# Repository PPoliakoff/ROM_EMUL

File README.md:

# ROM_EMUL
An emulator for the 27256 EPROM

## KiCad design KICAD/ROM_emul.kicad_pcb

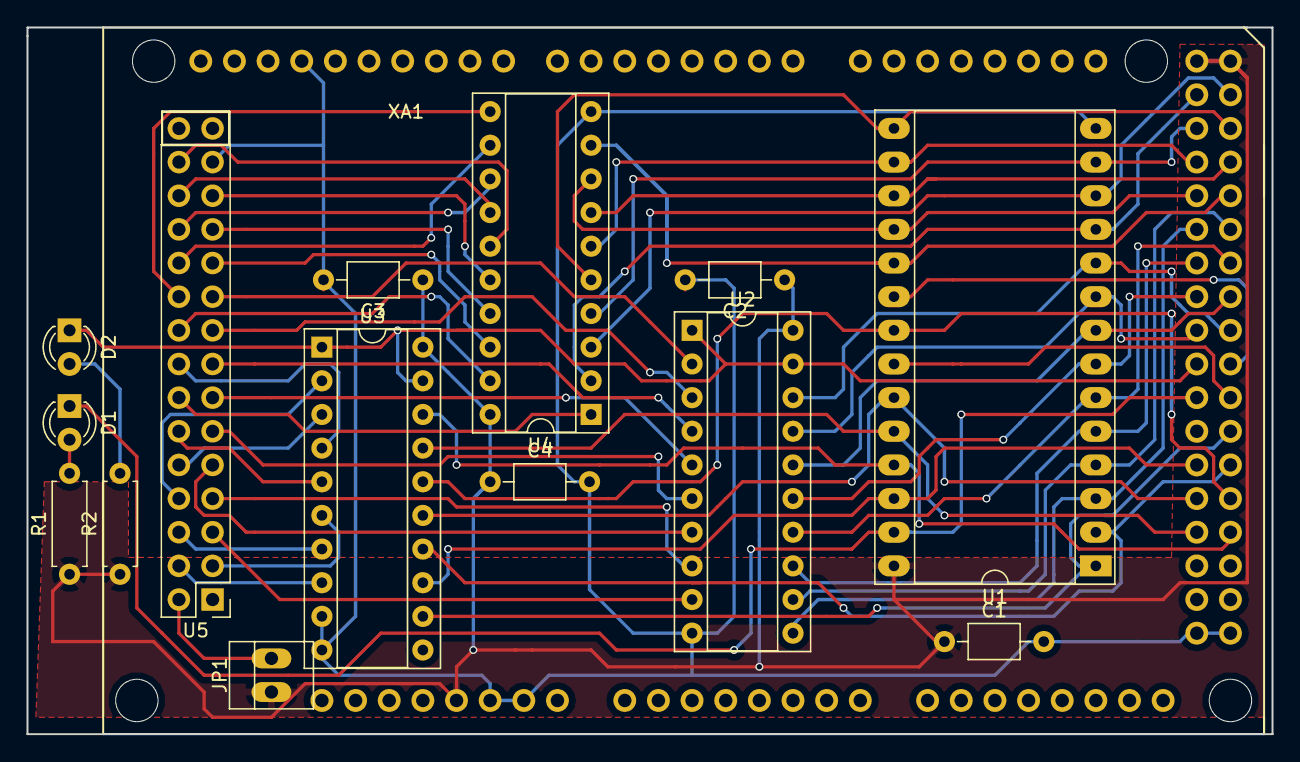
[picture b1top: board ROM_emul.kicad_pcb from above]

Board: 2 copper layers, 94.0 x 53.3 mm, 15 parts (0 on the bottom side), 57 nets.

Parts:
C1, C2, C3, C4: 100nF; C_Axial_L3.8mm_D2.6mm_P7.50mm_Horizontal
D1, D2: LED; LED_D3.0mm
JP1: VCCArduino; PINHEAD1-2
R1, R2: 680R; R_Axial_DIN0207_L6.3mm_D2.5mm_P7.62mm_Horizontal
U1: HM62256BLFP-7ULT; DIP-28_W15.24mm_Socket_LongPads
U2, U3, U4: 74LS541; DIP-20_W7.62mm_Socket
U5: 27C256Socket; Pin_Header_DIP28_plus2
XA1: Arduino_Mega2560_Shield; Arduino_Mega_cleaned

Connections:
/A0: U1.10, U2.18, XA1.D37
/A1: U1.9, U2.17, XA1.D36
/A2: U1.8, U2.16, XA1.D35
/A3: U1.7, U2.15, XA1.D34
/A4: U1.6, U2.14, XA1.D33
/A5: U1.5, U2.13, XA1.D32
/A6: U1.4, U2.12, XA1.D31
/A7: U1.3, U2.11, XA1.D30
/A8: U1.25, U3.18, XA1.D49
/A9: U1.24, U3.17, XA1.D48
/A10: U1.21, U3.16, XA1.D47
/A11: U1.23, U3.15, XA1.D46
/A12: U1.2, U3.14, XA1.D45
/A13: U1.26, U3.13, XA1.D44
/A14: U1.1, U3.12, XA1.D43
/D0: U1.11, U4.2, XA1.D22
/D1: U1.12, U4.3, XA1.D23
/D2: U1.13, U4.4, XA1.D24
/D3: U1.15, U4.5, XA1.D25
/D4: U1.16, U4.6, XA1.D26
/D5: U1.17, U4.7, XA1.D27
/D6: U1.18, U4.8, XA1.D28
/D7: U1.19, U4.9, XA1.D29
/RA0: U2.2, U5.10
/RA1: U2.3, U5.9
/RA2: U2.4, U5.8
/RA3: U2.5, U5.7
/RA4: U2.6, U5.6
/RA5: U2.7, U5.5
/RA6: U2.8, U5.4
/RA7: U2.9, U5.3
/RA8: U3.2, U5.25
/RA9: U3.3, U5.24
/RA10: U3.4, U5.21
/RA11: U3.5, U5.23
/RA12: U3.6, U5.2
/RA13: U3.7, U5.26
/RA14: U3.8, U5.27
/RD0: U4.18, U5.11
/RD1: U4.17, U5.12
/RD2: U4.16, U5.13
/RD3: U4.15, U5.15
/RD4: U4.14, U5.16
/RD5: U4.13, U5.17
/RD6: U4.12, U5.18
/RD7: U4.11, U5.19
GND: C1.2, C2.2, C3.2, C4.2, U1.14, U2.10, U3.9, U3.10, U4.10, U5.14, XA1.GND1, XA1.GND2, XA1.GND3, XA1.GND5, XA1.GND6
unnamed: D1.1, U1.27, XA1.D40
unnamed: D1.2, R1.2
unnamed: D2.1, U2.1, U2.19, U3.1, U3.19, XA1.D38
unnamed: D2.2, R2.2
unnamed: JP1.2, U5.28
unnamed: U1.20, XA1.D39
unnamed: U1.22, XA1.D41
unnamed: U4.1, U5.22
unnamed: U4.19, U5.20
VCC: C1.1, C2.1, C3.1, C4.1, JP1.1, R1.1, R2.1, U1.28, U2.20, U3.20, U4.20, XA1.5V1, XA1.5V3, XA1.5V4

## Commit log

2018-05-26 first PCB version
2018-05-26 PCB Correction to avoid USB Connector Overlap
2018-05-26 Arduino: added functions to set local / remote state
